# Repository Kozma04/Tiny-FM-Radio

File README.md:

# Tiny FM Radio v1 [Work in progress]
A small battery-powered FM Radio powered by the ATtiny3216 microcontroller.
Project sponsored by JLCPCB (https://jlcpcb.com/RAT)

It was originally intented to use the SI4703 FM tuner and some other ICs, but due to some PCB design mistakes and since this was originally a birthday project for my mother and I had to finish it ASAP, I was forced to drop some features for now and integrate in the project an FM tuner kit based on the HEX3653 IC I found at a local electronic components store.

This project's code is using SpenceKonde's megaTinyCore: https://github.com/SpenceKonde/megaTinyCore

# Present features
  * SH1106 monochrome OLED display (128x64 px, I2C interface)
  * TPA2005D1 1.4W audio amplifier fed by a PAM2401 5V/1A boost converter
  * 2W / 8Ohm speaker
  * 6 tactile buttons (up, down, left, right, ok and power)
  * 1200mAh LiPo battery
  * MCP73831 500mA LiPo / Li-Ion battery charger IC
  * Micro USB port for battery charging
  * AP2127K-3.3TRG1 3.3V / 400mA voltage regulator to supply the ICs. Uses the PAM2401 5V supply as input
  * ATtiny3216 microcontroller. Features:
    * Controls the HEX3653 FM tuner and the shutdown pins of the TPA2005D1 and PAM2401 ICs via a menu displayed on the OLED
    * Monitors the battery voltage
    * Shuts down the 5V supply when the battery voltage reaches a critical voltage

# Planned features (possible after fixing the PCB model)
  * SI4703-C19 FM tuner IC featuring volume control, RDS and more (needs external 32.768Khz oscillator)
  * Timekeeping using the MCP79402 real-time clock

Here is how the project looks like. __[Watch video!](https://youtu.be/wYINLay8BuY)__

This was my first 3D Printed case :)

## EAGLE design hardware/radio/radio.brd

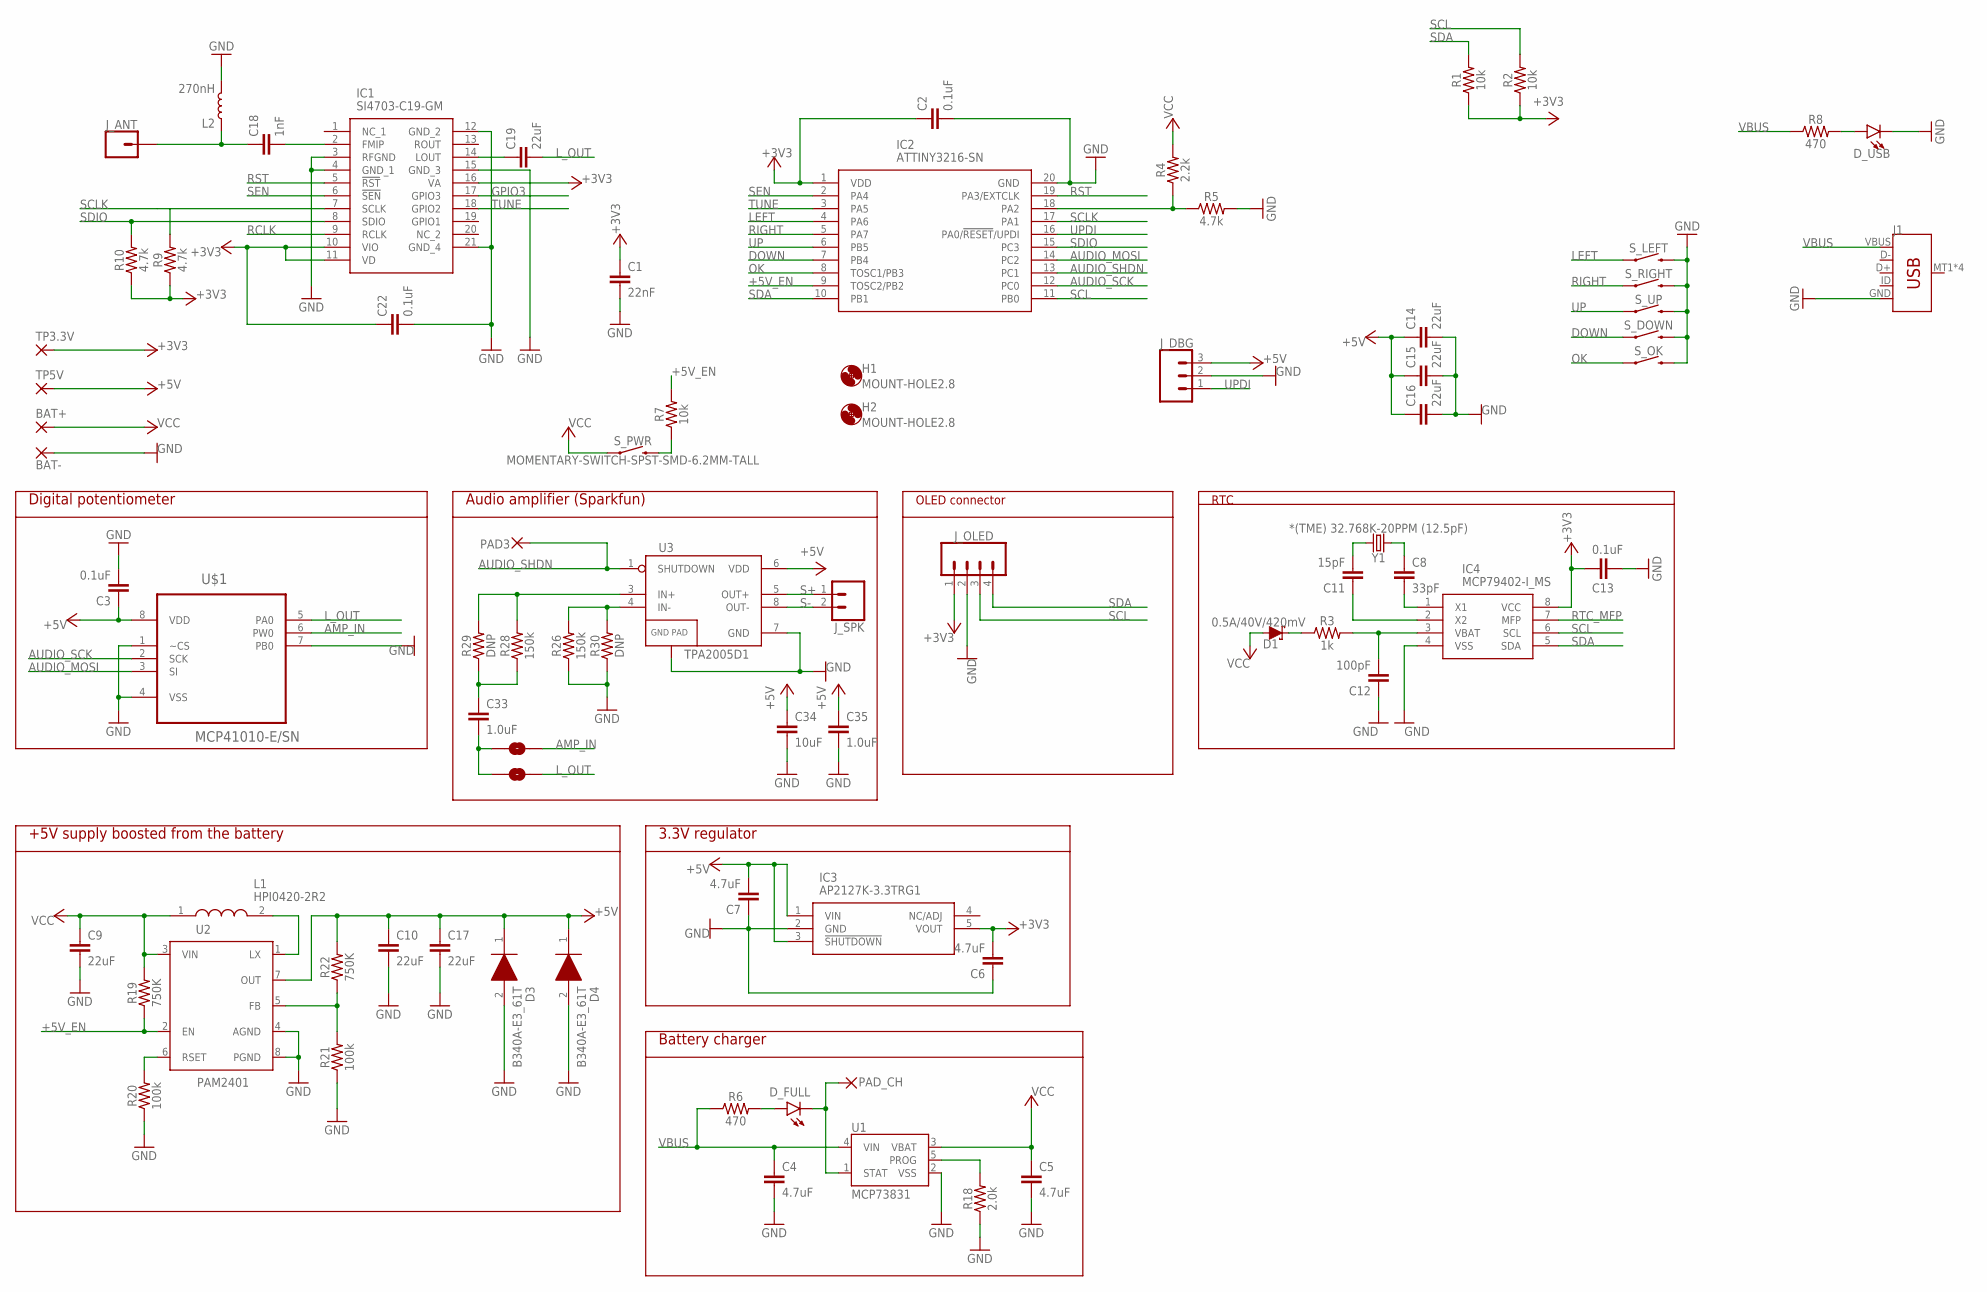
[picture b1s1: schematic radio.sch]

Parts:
BAT+: SMD2; SMD1,27-2,54
BAT-: SMD2; SMD1,27-2,54
C1: 22nF; 0603
C2, C3, C13, C22: 0.1uF; 0603
C4, C5, C6, C7: 4.7uF; 0603
C8: 33pF; 0603
C9, C10, C14, C15, C16, C17, C19: 22uF; 0805
C11: 15pF; 0603
C12: 100pF; 0603
C18: 1nF; 0603
C33, C35: 1.0uF; 0603
C34: 10uF; 0805
D1: 0.5A/40V/420mV; SOD-323
D3, D4: B340A-E3_61T; DIOM5127X229N
D_FULL: RED; LED_5MM
D_USB: LED5MM; LED_5MM
H1, H2: MOUNT-HOLE2.8; 2,8
IC1: SI4703-C19-GM; SI4703C19GM
IC2: ATTINY3216-SN; SOIC127P1030X265-20N
IC3: AP2127K-3.3TRG1; SOT95P282X145-5N
IC4: MCP79402-I_MS; SOP65P490X110-8N
J1: USB_MICRO-B_SMT; USB-MICROB
JP1, JP2: JUMPER-SMT_2_NO_NO-SILK; SMT-JUMPER_2_NO_NO-SILK
J_ANT: CONN_01; 1X01
J_DBG: CONN_03LOCK; 1X03_LOCK
J_OLED: CONN_04LOCK; 1X04_LOCK
J_SPK: CONN_02; 1X02
L1: HPI0420-2R2; HPI04202R2
L2: 270nH; 0805
PAD3: SMD2; SMD1,27-2,54
PAD_CH: SMD2; SMD1,27-2,54
R1, R2, R7: 10k; 0603
R3: 1k; 0603
R4: 2.2k; 0603
R5, R9, R10: 4.7k; 0603
R6, R8: 470; 0603
R18: 2.0k; 0603
R19, R22: 750K; 0603
R20, R21: 100k; 0603
R26, R28: 150k; 0603
R29, R30: DNP; 0603
S_DOWN: MOMENTARY-SWITCH-SPST-SMD-6.2MM-TALL; TACTILE_SWITCH_SMD_6.2MM_TALL
S_LEFT: MOMENTARY-SWITCH-SPST-SMD-6.2MM-TALL; TACTILE_SWITCH_SMD_6.2MM_TALL
S_OK: MOMENTARY-SWITCH-SPST-SMD-6.2MM-TALL; TACTILE_SWITCH_SMD_6.2MM_TALL
S_PWR: MOMENTARY-SWITCH-SPST-SMD-6.2MM-TALL; TACTILE_SWITCH_SMD_6.2MM_TALL
S_RIGHT: MOMENTARY-SWITCH-SPST-SMD-6.2MM-TALL; TACTILE_SWITCH_SMD_6.2MM_TALL
S_UP: MOMENTARY-SWITCH-SPST-SMD-6.2MM-TALL; TACTILE_SWITCH_SMD_6.2MM_TALL
TP3.3V, TP5V: SMD2; SMD1,27-2,54
U1: MCP73831; SOT23-5
U2: PAM2401; MSOP8
U3: TPA2005D1; POWER-SOP8
U$1: MCP41010-E/SN; SOIC127P600X175-8N
Y1: *(TME) 32.768K-20PPM (12.5pF); CRYSTAL-PTH-2X6-CYL

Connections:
+3V3: C1.1, C2.1, C3.1, C6.2, C13.2, C22.1, IC1.10 (VIO), IC1.11 (VD), IC1.16 (VA), IC2.1 (VDD), IC3.5 (VOUT), IC4.8 (VCC), J_OLED.1, R1.1, R2.1, R9.1, R10.1, TP3.3V.1, U$1.8 (VDD)
+5V: C7.2, C10.1, C14.1, C15.1, C16.1, C17.1, C34.1, C35.1, D3.1 (K), D4.1 (K), IC3.1 (VIN), IC3.3 (!SHUTDOWN), J_DBG.3, R22.2, TP5V.1, U2.7 (OUT), U3.6 (VDD)
+5V_EN: IC2.9 (TOSC2/PB2), R7.2, R19.1, U2.2 (EN)
AMP_IN: JP1.2, U$1.6 (PW0)
AUDIO_MOSI: IC2.14 (PC2), U$1.3 (SI)
AUDIO_SCK: IC2.12 (PC0), U$1.2 (SCK)
AUDIO_SHDN: IC2.13 (PC1), PAD3.1, U3.1 (SHUTDOWN)
DOWN: IC2.7 (PB4), S_DOWN.A2 (1)
GND: BAT-.1, C1.2, C2.2, C3.2, C4.2, C5.2, C6.1, C7.1, C9.2, C10.2, C12.1, C13.1, C14.2, C15.2, C16.2, C17.2, C22.2, C34.2, C35.2, D3.2 (A), D4.2 (A), D_USB.K (C), IC1.3 (RFGND), IC1.4 (GND_1), IC1.12 (GND_2), IC1.15 (GND_3), IC1.21 (GND_4), IC2.20 (GND), IC3.2 (GND), IC4.4 (VSS), J1.GND, J_DBG.2, J_OLED.2, L2.2, R5.2, R18.1, R20.1, R21.1, R26.1, R30.1, S_DOWN.B2 (2), S_LEFT.B2 (2), S_OK.B2 (2), S_RIGHT.B2 (2), S_UP.B2 (2), U1.2 (VSS), U2.4 (AGND), U2.8 (PGND), U3.7 (GND), U3.9 (GND), U$1.1 (~CS), U$1.4 (VSS), U$1.7 (PB0)
GPIO3: IC1.17 (GPIO3)
LEFT: IC2.4 (PA6), S_LEFT.A2 (1)
L_OUT: C19.2, JP2.2, U$1.5 (PA0)
unnamed: C18.2, IC1.2 (FMIP)
unnamed: C8.1, Y1.1
unnamed: C8.2, IC4.1 (X1)
unnamed: D_FULL.K (C), PAD_CH.1, U1.1 (STAT)
unnamed: D_FULL.A, R6.2
unnamed: C11.2, Y1.2
unnamed: C11.1, IC4.2 (X2)
unnamed: C12.2, IC4.3 (VBAT), R3.2
unnamed: D1.C, R3.1
unnamed: R18.2, U1.5 (PROG)
unnamed: R20.2, U2.6 (RSET)
unnamed: IC2.18 (PA2), R4.1, R5.1
unnamed: R7.1, S_PWR.B2 (2)
unnamed: D_USB.A, R8.2
unnamed: C18.1, J_ANT.1, L2.1
unnamed: C19.1, IC1.14 (LOUT)
unnamed: L1.2, U2.1 (LX)
unnamed: R21.2, R22.1, U2.5 (FB)
unnamed: R28.2, R29.2, U3.3 (IN+)
unnamed: R26.2, R30.2, U3.4 (IN-)
unnamed: C33.1, R28.1, R29.1
unnamed: C33.2, JP1.1, JP2.1
OK: IC2.8 (TOSC1/PB3), S_OK.A2 (1)
RCLK: IC1.9 (RCLK)
RIGHT: IC2.5 (PA7), S_RIGHT.A2 (1)
RST: IC1.5 (!RST), IC2.19 (PA3/EXTCLK)
RTC_MFP: IC4.7 (MFP)
S+: J_SPK.1, U3.5 (OUT+)
S-: J_SPK.2, U3.8 (OUT-)
SCL: IC2.11 (PB0), IC4.6 (SCL), J_OLED.3, R2.2
SCLK: IC1.7 (SCLK), IC2.17 (PA1), R9.2
SDA: IC2.10 (PB1), IC4.5 (SDA), J_OLED.4, R1.2
SDIO: IC1.8 (SDIO), IC2.15 (PC3), R10.2
SEN: IC1.6 (!SEN), IC2.2 (PA4)
TUNE: IC1.18 (GPIO2), IC2.3 (PA5)
UP: IC2.6 (PB5), S_UP.A2 (1)
UPDI: IC2.16 (PA0/!RESET!/UPDI), J_DBG.1
VBUS: C4.1, J1.VBUS, R6.1, R8.1, U1.4 (VIN)
VCC: BAT+.1, C5.1, C9.1, D1.A, L1.1, R4.2, R19.2, S_PWR.A2 (1), U1.3 (VBAT), U2.3 (VIN)

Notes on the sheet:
Digital potentiometer
Audio amplifier (Sparkfun)
+5V supply boosted from the battery
3.3V regulator
Battery charger
OLED connector
RTC

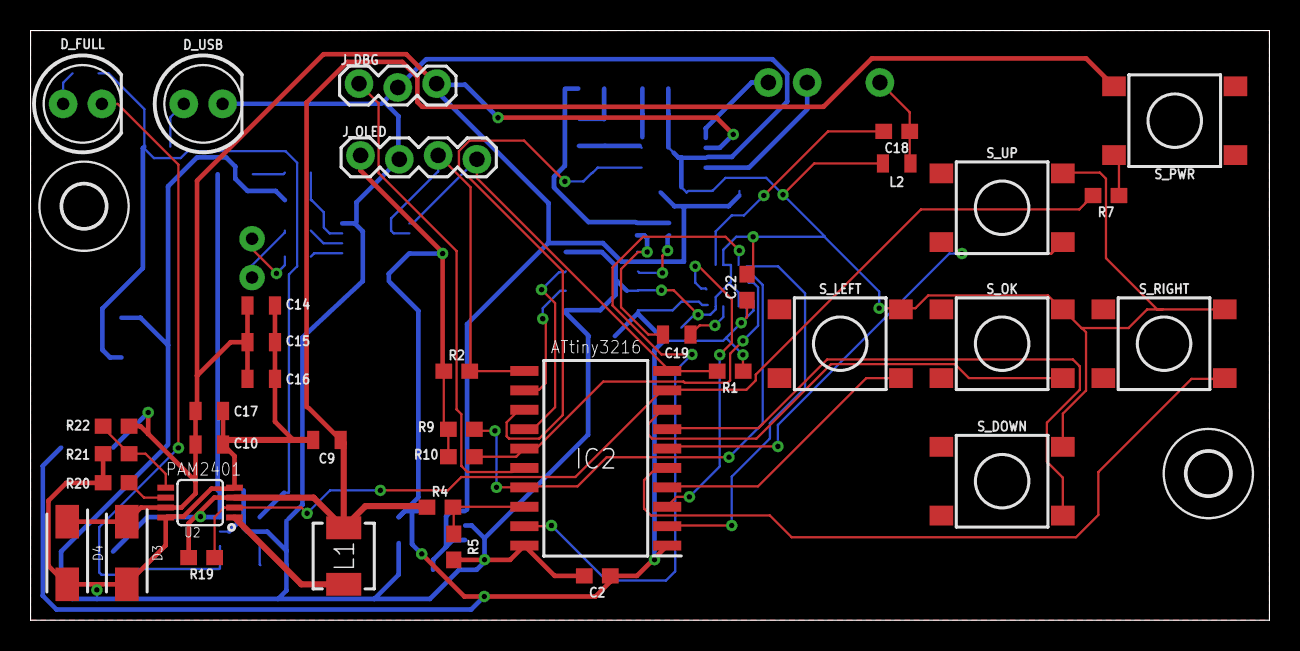
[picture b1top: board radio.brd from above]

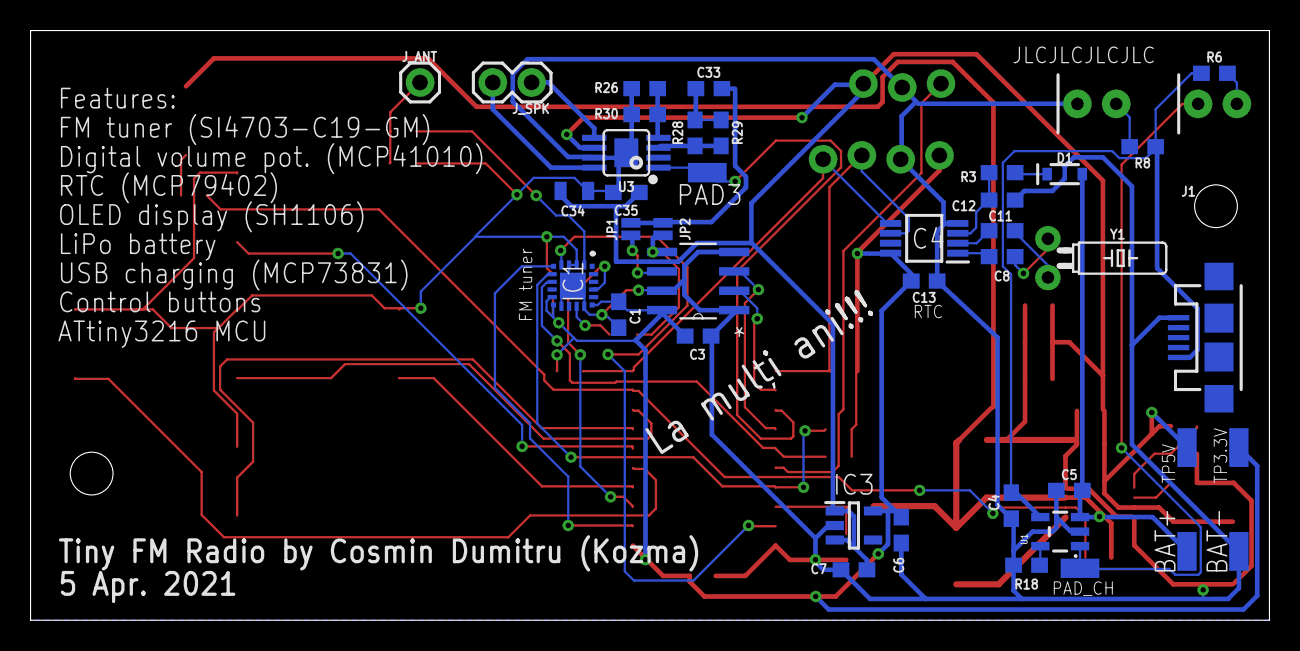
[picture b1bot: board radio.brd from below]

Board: 2 copper layers, 81.1 x 38.6 mm, 79 parts (40 on the bottom side), 48 nets.

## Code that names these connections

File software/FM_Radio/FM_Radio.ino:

#include <Wire.h>
#include "font5x7.h"
#include "tinytwi.h"
#include "SH1106.h"

#define PIN_PWR   PIN_PB2
#define PIN_BAT   PIN_PA2
#define PIN_OK    PIN_PB3
#define PIN_UP    PIN_PB5
#define PIN_DOWN  PIN_PB4
#define PIN_LEFT  PIN_PA6
#define PIN_RIGHT PIN_PA7
#define PIN_ASHDN PIN_PC1

#define PIN_PSW   PIN_PA4
#define PIN_VOLM  PIN_PC3
#define PIN_VOLP  PIN_PC0
#define PIN_SEEKM PIN_PA1
#define PIN_SEEKP PIN_PA3

enum Action {
    LEFT, RIGHT, OK
};

struct Entry {
    char name[24] = {0};
    void (*callback)(Entry*, Action) = 0;
};

struct Menu {
    char name[16] = {0};
    Entry *entries[7];
    uint8_t nEntries;
};

Menu *menu;

uint8_t hovered;
bool mute = false;
int volume;

void renderMenu() {
    oled.clear();
    oled.setCursor(0, 0);
    oled.fontColor = INVERSE;
    oled.backColor = BLACK;
    oled.println(menu->name);
    for(int i = 0; i < menu->nEntries; i++) {
        if(i == hovered) oled.backColor = WHITE;
        oled.println(menu->entries[i]->name);
        if(i == hovered) oled.backColor = BLACK;
    }
}

void menuUp() {
    if(hovered > 0) hovered--;
    else hovered = menu->nEntries - 1;
}

void menuDown() {
    if(hovered < (menu->nEntries) - 1) hovered++;
    else hovered = 0;
}

void menuInteract(Action action) {
    if(menu->entries[hovered]->callback != 0)
        menu->entries[hovered]->callback(menu->entries[hovered], action);
}

void setMenu(Menu *newMenu) {
    hovered = 0;
    menu = newMenu;
}

void press(int pin) {
    digitalWrite(pin, LOW);
    pinMode(pin, OUTPUT);
    delay(100);
    pinMode(pin, INPUT);
    delay(100);
}

Menu home;
Entry eBattery;
Entry eShutdown;
Entry eMute;
Entry eVolume;
Entry eSeek;
Entry ePsw;

uint32_t t;

void shutdown() {
    oled.command(SH1106_DISPLAYOFF);
    delay(100);
    PORTB.OUTCLR = 1 << 2;
    for(;;);
}

void shutdownCallback(Entry *entry, Action action) {
    if((PORTB.IN & (1 << 3)) == 0) {
        t = millis();
        while((PORTB.IN & (1 << 3)) == 0) {
            if(millis() - t > 1500) {
                shutdown();
            }
        }
    }
}

void muteCallback(Entry *entry, Action action) {
    mute = !mute;
    if(mute) {
        strcpy(eMute.name, " Mute: DA");
        digitalWrite(PIN_ASHDN, LOW);
    }
    else {
        strcpy(eMute.name, " Mute: NU");
        digitalWrite(PIN_ASHDN, HIGH);
    }
}

void volumeCallback(Entry *entry, Action action) {
    if(action == LEFT) {
        press(PIN_VOLM);
    }
    else if(action == RIGHT) {
        press(PIN_VOLP);
    }
}

void seekCallback(Entry *entry, Action action) {
    if(action == LEFT) {
        press(PIN_SEEKM);
    }
    else if(action == RIGHT) {
        press(PIN_SEEKP);
    }
}

void pswCallback(Entry *entry, Action action) {
    press(PIN_PSW);
}

void initMenu() {
    setMenu(&home);
    strcpy(home.name, "Radio FM");
    home.nEntries = 6;
    home.entries[0] = &eBattery;
    home.entries[1] = &eMute;
    home.entries[2] = &eVolume;
    home.entries[3] = &eSeek;
    home.entries[4] = &ePsw;
    home.entries[5] = &eShutdown;

    strcpy(eBattery.name, " [no battery data]");
    strcpy(eMute.name, " Mute: NU");
    strcpy(eVolume.name, " Volum [- / +]");
    strcpy(eShutdown.name, " Oprire");
    strcpy(eSeek.name, " Canal [- / +]");
    strcpy(ePsw.name, " PSW (buton radio)");
    eShutdown.callback = shutdownCallback;
    eMute.callback = muteCallback;
    eVolume.callback = volumeCallback;
    eSeek.callback = seekCallback;
    ePsw.callback = pswCallback;
}

int appendInt(char *c, int t, int pos) {
    int p10 = pow(10, getNc(t) - 1);
    while(p10 > 0) {
        c[pos++] = '0' + (t / p10 % 10);
        p10 /= 10;
    }
    return pos;
}

void setup() {
    pinMode(PIN_ASHDN, OUTPUT);
    digitalWrite(PIN_ASHDN, LOW);
    PORTB.DIRCLR = 1 << 2;
    PORTB.DIRCLR = 1 << 5; // UP
    PORTB.PIN5CTRL = 1 << 3;
    uint32_t t = millis();
    bool ok = true;
    while(millis() - t < 1000) {
        if((PORTB.IN & (1 << 5)) != 0) {
            ok = false;
        }
    }
    if(!ok) {
        PORTB.DIRSET = 1 << 2;
        PORTB.OUTCLR = 1 << 2;
        for(;;);
    }

    PORTB.DIRSET = 1 << 2;
    PORTB.OUTSET = 1 << 2;
    PORTB.OUTCLR = 1 << 2;
    PORTB.OUTSET = 1 << 2;

    PORTB.DIRCLR = 1 << 3;
    PORTB.PIN3CTRL = 1 << 3;

    pinMode(PIN_UP, INPUT_PULLUP);
    pinMode(PIN_DOWN, INPUT_PULLUP);
    pinMode(PIN_LEFT, INPUT_PULLUP);
    pinMode(PIN_RIGHT, INPUT_PULLUP);
    analogReadResolution(10);

    TinyWire.begin();
    TinyWire.setSpeed(FAST_MODE);
    oled.setFont(font5x7, 5, 8, 1);

    oled.begin(FRAMEBUFFER_INT);

    oled.clear();
    oled.setCursor(0, 0);
    oled.println("Initializare...");
    oled.display();

    delay(500);
    oled.command(SH1106_DISPLAYOFF);
    delay(500);
    oled.command(SH1106_DISPLAYON);

    // set display orientation
    oled.command(0xc0 | 0x08);
    oled.command(0xa0 | 0x01);

    initMenu();

    pinMode(PIN_ASHDN, OUTPUT);
    digitalWrite(PIN_ASHDN, HIGH);
    for(int i = 0; i < 20; i++) press(PIN_VOLM);
}

uint8_t getNc(uint8_t x) {
    if(x >= 100) return 3;
    if(x >= 10) return 2;
    return 1;
}

uint32_t lastPress;
uint32_t f;

float bat = 1000;
float lowThreshold = 3.15; // Battery voltage considered low
float criticalThreshold = 3; // shutdown voltage

void loop() {
    f++;
    if(f % 10 == 0) {
        uint32_t val = 0;
        for(int i = 0; i < 10; i++)
            val += analogRead(PIN_BAT);
        val /= 10;
        bat = (val / 1024.f * 3.3f) * 6900.f / 4700.f;
        int p = min(100, max(0, int((bat - 3.f) / (4.2f - 3.f) * 100.f)));
        memset(eBattery.name, 0, 24);
        strcat(eBattery.name, " Bat.: ");
        int pos = 7;
        pos = appendInt(eBattery.name, int(bat), pos);
        eBattery.name[pos++] = '.';
        pos = appendInt(eBattery.name, int(bat * 100) % 100, pos);
        eBattery.name[pos++] = 'v';
        eBattery.name[pos++] = ' ';
        eBattery.name[pos++] = '/';
        eBattery.name[pos++] = ' ';
        pos = appendInt(eBattery.name, p, pos);
        eBattery.name[pos++] = '%';
    }

    /*
    oled.clear();
    oled.setCursor(0, 0);
    oled.fontColor = INVERSE;
    oled.backColor = WHITE;
    oled.print(" Readings:");
    oled.backColor = BLACK;
    oled.println(f);

    oled.print("Battery: ");
    oled.print(bat);
    oled.print("v / ");
    oled.print(int((bat - 3.f) / (4.2f - 3.f) * 100.f));
    oled.println("%");

    if(digitalRead(PIN_UP) == LOW) {
        press(PIN_VOLP);
        oled.println("Vol up");
    }
    else if(digitalRead(PIN_DOWN) == LOW) {
        press(PIN_VOLM);
        oled.println("Vol down");
    }
    else if(digitalRead(PIN_LEFT) == LOW) {
        press(PIN_SEEKM);
        oled.println("Seek -");
    }
    else if(digitalRead(PIN_RIGHT) == LOW) {
        press(PIN_SEEKP);
        oled.println("Seek +");
    }

    oled.display();
    delay(1000);*/

    if(millis() - lastPress >= 300) {
        bool pressed = false;
        if(digitalRead(PIN_UP) == LOW) {
            menuUp();
            pressed = true;
        }
        else if(digitalRead(PIN_DOWN) == LOW) {
            menuDown();
            pressed = true;
        }
        else if(digitalRead(PIN_LEFT) == LOW) {
            menuInteract(LEFT);
            pressed = true;
        }
        else if(digitalRead(PIN_RIGHT) == LOW) {
            menuInteract(RIGHT);
            pressed = true;
        }
        else if(digitalRead(PIN_OK) == LOW) {
            menuInteract(OK);
            pressed = true;
        }
        if(pressed) lastPress = millis();
    }

    renderMenu();
    if(bat < lowThreshold) {
        if(f % 80 > 40) {
            oled.invert(true);
            oled.backColor = WHITE;
        }
        else {
            oled.invert(false);
            oled.backColor = WHITE;
        }
        oled.print("BATERIE DESCARCATA"); // low battery
        oled.backColor = BLACK;
    }
    else oled.invert(false);
    if(bat < criticalThreshold) shutdown();
    oled.display();
}

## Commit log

2021-06-10 Added code and media files
2021-06-10 Removed video files

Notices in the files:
parts and their libraries:
SparkFun-Capacitors: Licensing: Creative Commons ShareAlike 4.0 International - https://creativecommons.org/licenses/by-sa/4.0
